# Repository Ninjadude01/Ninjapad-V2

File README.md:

# Ninjapad-V2
The Ninjapad-V2 is a wireless macropad with 6 switches, a customizable knob, and a 0.91" oled display! It is fully hot-swappable, uses a 3.7V 600mAh rechargable lithium battery, and has mini-leds. By using ZMK firmware, it can wirelessly connect to your device and function as usual.

This is my second time creating a macropad; my first design was very basic and bland. I wanted to create something that was more advanced, had more features, and looked cooler, which is why I decided to have another go though NinjapadV2.

# Fallout Zine

# Renders

# Layout
I decided to go with a 6-key layout as I do not need too many macros. It's a good mix between looking clean, while providing functionality.

# Schematic
The schematic and PCB for NinjapadV2 was designed in kicad, and a modified 3x3 matrix is used. **Note:** The wiring for the lithium battery was not included in the schematic. The positive side of the battery is wired to the bat+ pad on the bottom of the xiao, and the negative side is wired to bat-.

# PCB
The xiao is located on the top right corner for easy access when you need to plug it in. The silkscreen includes the name "NinjaboardV2" written diagonally, the Hackclub/Nasa logo, and a Hackclub Milkyway star sticker.

# Assembly Guide
1. Solder the headerpins to the xiao, then the xiao to the pcb. Solder the rotary encoder, kailh hot swap sockets, oled display, mini leds, diodes, resistor, and oled display to the pcb as well. Make sure to cut off any legs or pins that are sticking out.
2. Solder the positive end of your litium battery to bat+ on the underside of the xiao, and the negative side to bat-.
3. After printing out the peices, use a soldering iron set to 200°C to slowly press in the 4 heatset inserts into their designated locations in the main body of the macropad.
4. Snap the keyswitches onto the plate, and place it ontop of the pcb, making sure to align the keyswich pins into the hot swap sockets. Place the knob cap over the rotary encoder.
5. Place the battery in the designated location in the base, and cover it with the connected pcb and plate. Screw in the plate using the m2 screws.
   
# Firmware Flashing Steps
1. Download the .uf2 file found in the Firmware folder.
2. Plug the xiao into your device. Press the tiny reset button twice, and a new usb drive called Xiao-BLE should appear.
3. Copy and paste the .uf2 file into the drive.
4. Open the bluetooth settings on your device, and the name "NinjapadV2" should appear. Click to pair.
5. Your new NinjapadV2 should be ready to go!
   
# BOM
|Item|Part Name              |Quantity|Description                    |Cost (USD)|Link                                                                                                                                                                                                                                                                                                                                                                                                                                                                                                                                                                                                                                                                                                       |
|----|-----------------------|--------|-------------------------------|----------|-----------------------------------------------------------------------------------------------------------------------------------------------------------------------------------------------------------------------------------------------------------------------------------------------------------------------------------------------------------------------------------------------------------------------------------------------------------------------------------------------------------------------------------------------------------------------------------------------------------------------------------------------------------------------------------------------------------|
|1   |Custom PCB             |5       |Printed Circut Board           |$2        |https://jlcpcb.com/                                                                                                                                                                                                                                                                                                                                                                                                                                                                                                                                                                                                                                                                                        |
|2   |Xiao nRF52840          |1       |Microcontroller                |$13.56    |https://www.aliexpress.com/item/1005006988944671.html?spm=a2g0o.productlist.main.1.26c47362JhrW93&algo_pvid=a8527b8d-12b0-40b0-9e80-fb8d44be5472&algo_exp_id=a8527b8d-12b0-40b0-9e80-fb8d44be5472-0&pdp_ext_f=%7B%22order%22%3A%22344%22%2C%22eval%22%3A%221%22%2C%22fromPage%22%3A%22search%22%7D&pdp_npi=6%40dis%21CAD%2137.78%2118.89%21%21%21179.99%2189.99%21%402101ea8c17808543304102701ea0b8%2112000051690441650%21sea%21CA%217451194651%21X%211%210%21n_tag%3A-29919%3Bd%3A8fd05d1b%3Bm03_new_user%3A-29895&curPageLogUid=pFjYSvoeQgMf&utparam-url=scene%3Asearch%7Cquery_from%3A%7Cx_object_id%3A1005006988944671%7C_p_origin_prod%3A                                                             |
|3   |Gateron Yellow Switches|5       |Key switches, serve as input   |$6.24     |https://www.aliexpress.com/item/1005008685972487.html?spm=a2g0o.productlist.main.3.65732540dYl2GP&algo_pvid=cc874fa9-8f9a-4fc1-8beb-a167023295a2&algo_exp_id=cc874fa9-8f9a-4fc1-8beb-a167023295a2-2&pdp_ext_f=%7B%22order%22%3A%22234%22%2C%22spu_best_type%22%3A%22price%22%2C%22eval%22%3A%221%22%2C%22fromPage%22%3A%22search%22%7D&pdp_npi=6%40dis%21CAD%2120.31%218.70%21%21%2196.76%2141.44%21%402101c59117808545475013713e48d3%2112000046260429586%21sea%21CA%217451194651%21X%211%210%21n_tag%3A-29919%3Bd%3A8fd05d1b%3Bm03_new_user%3A-29895%3BpisId%3A5000000208502900&curPageLogUid=W5X1cJpDGLWv&utparam-url=scene%3Asearch%7Cquery_from%3A%7Cx_object_id%3A1005008685972487%7C_p_origin_prod%3A|
|4   |Blank White Keycaps    |10      |Protection                     |$4.59     |https://www.aliexpress.com/item/1005004902730327.html?spm=a2g0o.productlist.main.8.399aBeKpBeKpgf&algo_pvid=bc9fbdb6-efda-447c-8913-e4d38307cf85&algo_exp_id=bc9fbdb6-efda-447c-8913-e4d38307cf85-8&pdp_ext_f=%7B%22order%22%3A%22887%22%2C%22spu_best_type%22%3A%22price%22%2C%22eval%22%3A%221%22%2C%22fromPage%22%3A%22search%22%7D&pdp_npi=6%40dis%21CAD%216.05%216.05%21%21%214.25%214.25%21%40210328d417808546269024304e96cf%2112000033043765234%21sea%21CA%217451194651%21X%211%210%21n_tag%3A-29919%3Bd%3A8fd05d1b%3Bm03_new_user%3A-29895&curPageLogUid=ISz0zQTMmX4W&utparam-url=scene%3Asearch%7Cquery_from%3A%7Cx_object_id%3A1005004902730327%7C_p_origin_prod%3A                              |
|5   |Kailh Hot-swap Sockets |10      |Allows hot-swapping of switches|$3.17     |https://www.aliexpress.com/item/1005007232040760.html?spm=a2g0o.order_list.order_list_main.35.38ca1802hz0ATr                                                                                                                                                                                                                                                                                                                                                                                                                                                                                                                                                                                               |
|6   |Rotary Encoder         |1       |You can rotate it              |$5.53     |https://www.digikey.ca/en/products/detail/alps-alpine/EC11E15244B2/19529170                                                                                                                                                                                                                                                                                                                                                                                                                                                                                                                                                                                                                                |
|7   |Encoder Knob cap       |1       |Protection                     |$4.08     |https://www.aliexpress.com/item/1005006531154080.html?spm=a2g0o.order_list.order_list_main.5.256d1802T4w9tK                                                                                                                                                                                                                                                                                                                                                                                                                                                                                                                                                                                                |
|8   |M2 Heatset Inserts     |100     |Threaded metal hole, L3xOD 3.2 |$3.17     |https://www.aliexpress.com/item/1005006838108683.html?spm=a2g0o.cart.0.0.1c1b38dalGfMuU&mp=1&pdp_npi=6%40dis%21CAD%21CAD+5.20%21CAD+5.20%21%21CAD+5.20%21%21%21%4021033d9d17760010503013922ef23d%2112000038467725083%21ct%21CA%217451194651%21%211%210%21                                                                                                                                                                                                                                                                                                                                                                                                                                                  |
|9   |M2 Screw               |50      |4mm long screw                 |$1.51     |https://www.aliexpress.com/item/32973784147.html?spm=a2g0o.productlist.main.1.304apnmvpnmvhX&algo_pvid=8e4bcfb2-c0a1-48f2-ad5e-84593aa7934a&algo_exp_id=8e4bcfb2-c0a1-48f2-ad5e-84593aa7934a-0&pdp_ext_f=%7B%22order%22%3A%227855%22%2C%22spu_best_type%22%3A%22price%22%2C%22eval%22%3A%221%22%2C%22fromPage%22%3A%22search%22%7D&pdp_npi=6%40dis%21CAD%212.26%212.26%21%21%211.60%211.60%21%402101e2b417760020144634724ef5ec%2112000024189797294%21sea%21CA%217451194651%21X%211%210%21n_tag%3A-29912%3Bd%3A8fd05d1b%3Bm03_new_user%3A-29895&curPageLogUid=kvh1vbqAtJaq&utparam-url=scene%3Asearch%7Cquery_from%3A%7Cx_object_id%3A32973784147%7C_p_origin_prod%3A                                       |
|10  |1N4148 Diodes          |100     |Prevent kb switch ghosting     |$1.36     |https://www.aliexpress.com/item/4001126137167.html?spm=a2g0o.productlist.main.5.79e7482dKtCmX2&algo_pvid=318c005b-3483-41ec-a5f5-6fc5037bbfee&algo_exp_id=318c005b-3483-41ec-a5f5-6fc5037bbfee-4&pdp_ext_f=%7B%22order%22%3A%221233%22%2C%22eval%22%3A%221%22%2C%22fromPage%22%3A%22search%22%7D&pdp_npi=6%40dis%21CAD%211.89%211.89%21%21%211.33%211.33%21%402101c44517808548772467266e39aa%2110000014629985518%21sea%21CA%217451194651%21X%211%210%21n_tag%3A-29919%3Bd%3A8fd05d1b%3Bm03_new_user%3A-29895&curPageLogUid=gGlbxJ80xgK9&utparam-url=scene%3Asearch%7Cquery_from%3A%7Cx_object_id%3A4001126137167%7C_p_origin_prod%3A                                                                       |
|11  |0.91 inch OLED 128x32  |1       | 0.91" Display Blue            |$2.07     |https://www.aliexpress.com/item/1005004572487969.html?spm=a2g0o.productlist.main.5.28c7bb6tbb6tCz&algo_pvid=24ca4424-442d-4cf5-a3ab-500681c94454&algo_exp_id=24ca4424-442d-4cf5-a3ab-500681c94454-4&pdp_ext_f=%7B%22order%22%3A%223252%22%2C%22spu_best_type%22%3A%22price%22%2C%22eval%22%3A%221%22%2C%22fromPage%22%3A%22search%22%7D&pdp_npi=6%40dis%21CAD%213.55%213.55%21%21%212.45%212.45%21%402101d9ef17839472626645394e0f27%2112000029674573174%21sea%21CA%217451194651%21X%211%210%21n_tag%3A-29919%3Bd%3Ab58c364f%3Bm03_new_user%3A-29895&curPageLogUid=NmXXvZPH981j&utparam-url=scene%3Asearch%7Cquery_from%3A%7Cx_object_id%3A1005004572487969%7C_p_origin_prod%3A                             |
|12  |SK6812 Mini-E RGBW     |20      |RGB Lights                     |$2.50     |https://www.aliexpress.com/item/1005005193716172.html?spm=a2g0o.productlist.main.3.a076T6PrT6PrJF&algo_pvid=f109bb1d-d3c7-435c-bcb0-0381f6c9a9b2&algo_exp_id=f109bb1d-d3c7-435c-bcb0-0381f6c9a9b2-2&pdp_ext_f=%7B%22order%22%3A%22340%22%2C%22spu_best_type%22%3A%22price%22%2C%22eval%22%3A%221%22%2C%22fromPage%22%3A%22search%22%7D&pdp_npi=6%40dis%21CAD%215.98%215.79%21%21%2128.49%2127.59%21%402101e2b417808554316812966ec6c8%2112000032072424634%21sea%21CA%217451194651%21X%211%210%21n_tag%3A-29919%3Bd%3A8fd05d1b%3Bm03_new_user%3A-29895&curPageLogUid=HfZZAMs5AZij&utparam-url=scene%3Asearch%7Cquery_from%3A%7Cx_object_id%3A1005005193716172%7C_p_origin_prod%3A                            |
|13  |Anti-slip Rubber pads  |50      |Prevent sliding                |$1.82     |https://www.aliexpress.com/item/1005008384264974.html?spm=a2g0o.productlist.main.5.311e6eceErL6jS&algo_pvid=f31db234-3426-481a-8b61-49df5adcf490&algo_exp_id=f31db234-3426-481a-8b61-49df5adcf490-4&pdp_ext_f=%7B%22order%22%3A%22986%22%2C%22spu_best_type%22%3A%22price%22%2C%22eval%22%3A%221%22%2C%22fromPage%22%3A%22search%22%7D&pdp_npi=6%40dis%21CAD%212.28%211.85%21%21%211.60%211.30%21%402103129017808559113205351eb105%2112000044801616190%21sea%21CA%217451194651%21X%211%210%21n_tag%3A-29919%3Bd%3A8fd05d1b%3Bm03_new_user%3A-29895&curPageLogUid=poOU9u8loeG4&utparam-url=scene%3Asearch%7Cquery_from%3A%7Cx_object_id%3A1005008384264974%7C_p_origin_prod%3A                              |
|14  |Lithium Battery        |1       |3.7V 600mAh rechargable        |$6.19     |https://www.aliexpress.com/item/1005009734239153.html?spm=a2g0o.productlist.main.1.4e3558pL58pLhQ&algo_pvid=233dbada-a420-4553-8722-a78dadbc389f&algo_exp_id=233dbada-a420-4553-8722-a78dadbc389f-0&pdp_ext_f=%7B%22order%22%3A%22504%22%2C%22spu_best_type%22%3A%22price%22%2C%22eval%22%3A%221%22%2C%22fromPage%22%3A%22search%22%7D&pdp_npi=6%40dis%21CAD%2111.50%218.62%21%21%2154.81%2141.11%21%40210311c217808574206456289eb7b7%2112000049985375130%21sea%21CA%217451194651%21X%211%210%21n_tag%3A-29919%3Bd%3A8fd05d1b%3Bm03_new_user%3A-29895&curPageLogUid=wFmcyCzzIm6O&utparam-url=scene%3Asearch%7Cquery_from%3A%7Cx_object_id%3A1005009734239153%7C_p_origin_prod%3A#nav-description           |
|    |                       |        |                               |          |                                                                                                                                                                                                                                                                                                                                                                                                                                                                                                                                                                                                                                                                                                           |
|    |                       |        |Total Cost                     |$57.79    |

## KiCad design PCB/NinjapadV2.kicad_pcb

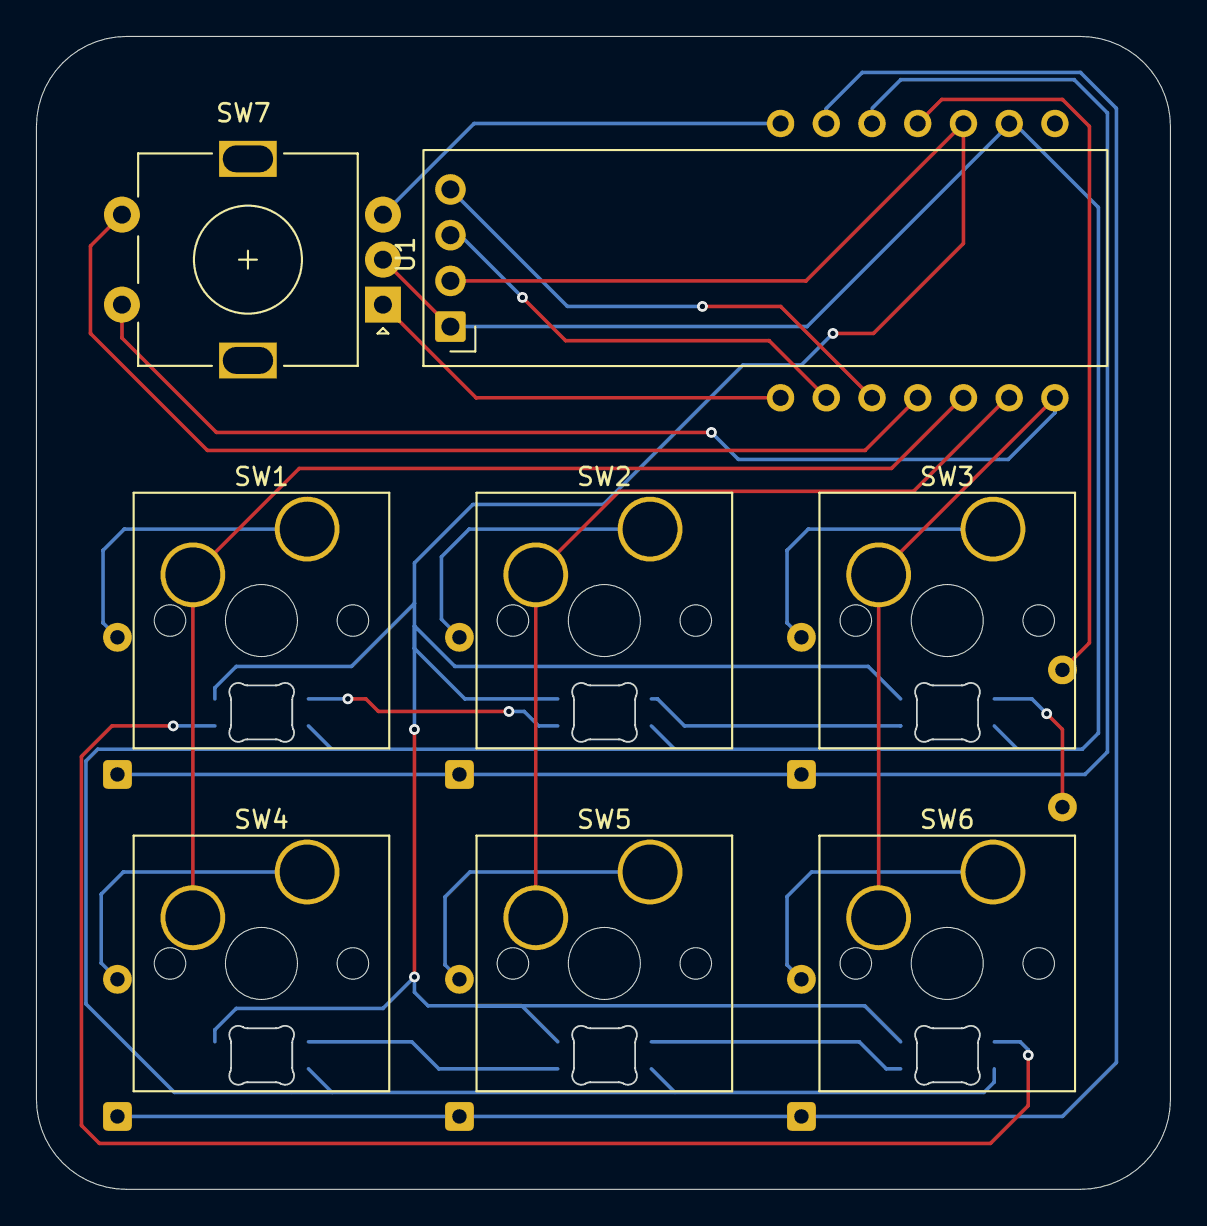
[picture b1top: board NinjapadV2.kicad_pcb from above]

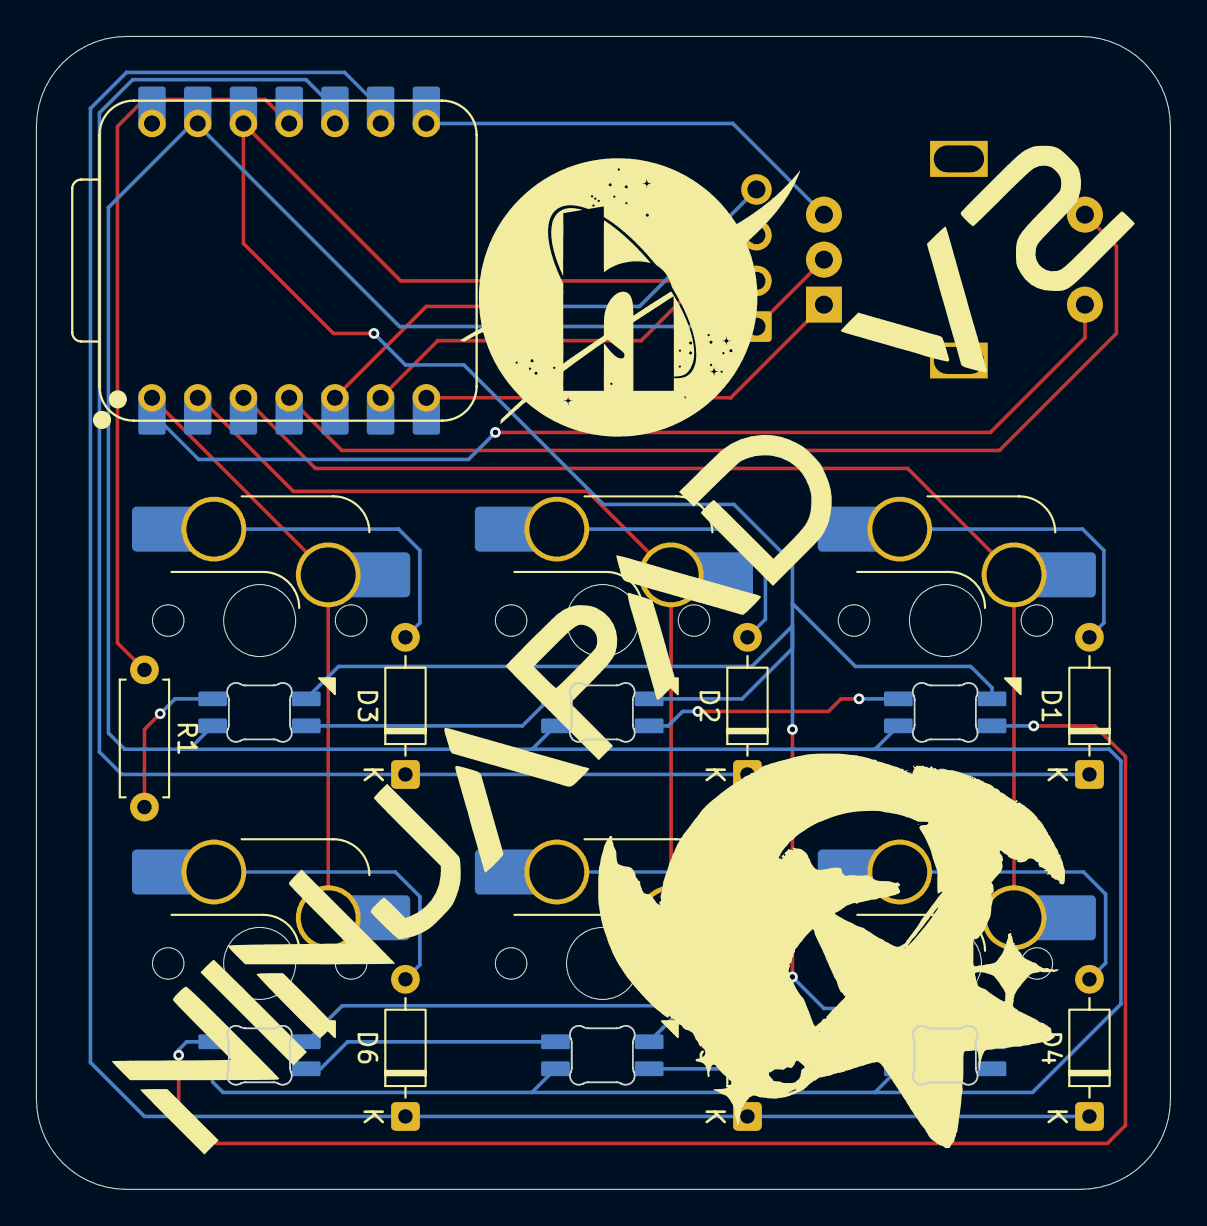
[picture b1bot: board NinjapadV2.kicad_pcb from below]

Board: 2 copper layers, 63.0 x 64.0 mm, 22 parts (8 on the bottom side), 25 nets.

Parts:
D1, D2, D3, D4, D5, D6: D; D_DO-35_SOD27_P7.62mm_Horizontal
IC1: XIAO-nRF52840-DIP
L1, L2, L3, L4, L5, L6: SK6812MINI-E; MX_SK6812MINI-E_REV
R1: 330 R; R_Axial_DIN0207_L6.3mm_D2.5mm_P7.62mm_Horizontal
SW1, SW2, SW3, SW4, SW5, SW6: SW_Push_45deg; SW_Hotswap_Kailh_MX_Plated_1.00u
SW7: RotaryEncoder_Switch; RotaryEncoder_Alps_EC11E-Switch_Vertical_H20mm
U1: 0.91"; ER_OLEDM0.91_1x-I2C

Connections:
3.3V: IC1.12 (3V3), L1.3 (VDD), L2.3 (VDD), L3.3 (VDD), L4.3 (VDD), L5.3 (VDD), L6.3 (VDD), U1.2 (VCC)
GND: IC1.13 (GND), L1.1 (VSS), L2.1 (VSS), L3.1 (VSS), L4.1 (VSS), L5.1 (VSS), L6.1 (VSS), SW7.C, U1.1 (GND)
Knob A: IC1.7 (D6), SW7.A
Knob B: IC1.8 (D7), SW7.B
unnamed: D1.2 (A), SW1.2
unnamed: D2.2 (A), SW2.2
unnamed: D3.2 (A), SW3.2
unnamed: D4.2 (A), SW4.2
unnamed: D5.2 (A), SW5.2
unnamed: D6.2 (A), SW6.2
unnamed: L1.2 (DIN), R1.2
unnamed: L1.4 (DOUT), L2.2 (DIN)
unnamed: L2.4 (DOUT), L3.2 (DIN)
unnamed: L3.4 (DOUT), L4.2 (DIN)
unnamed: L4.4 (DOUT), L5.2 (DIN)
unnamed: L5.4 (DOUT), L6.2 (DIN)
RGB: IC1.11 (D10), R1.1
SCL: IC1.6 (D5_SCL), U1.3 (SCL)
SDA: IC1.5 (D4_SDA), U1.4 (SDA)
col1: IC1.3 (D2), SW1.1, SW4.1
col2: IC1.2 (D1), SW2.1, SW5.1
col3: IC1.1 (D0), SW3.1, SW6.1, SW7.S2
row1: IC1.4 (D3), SW7.S1
row2: D1.1 (K), D2.1 (K), D3.1 (K), IC1.10 (D9)
row3: D4.1 (K), D5.1 (K), D6.1 (K), IC1.9 (D8)

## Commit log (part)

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2026-06-08 Create temp
2026-06-08 Create tmep
